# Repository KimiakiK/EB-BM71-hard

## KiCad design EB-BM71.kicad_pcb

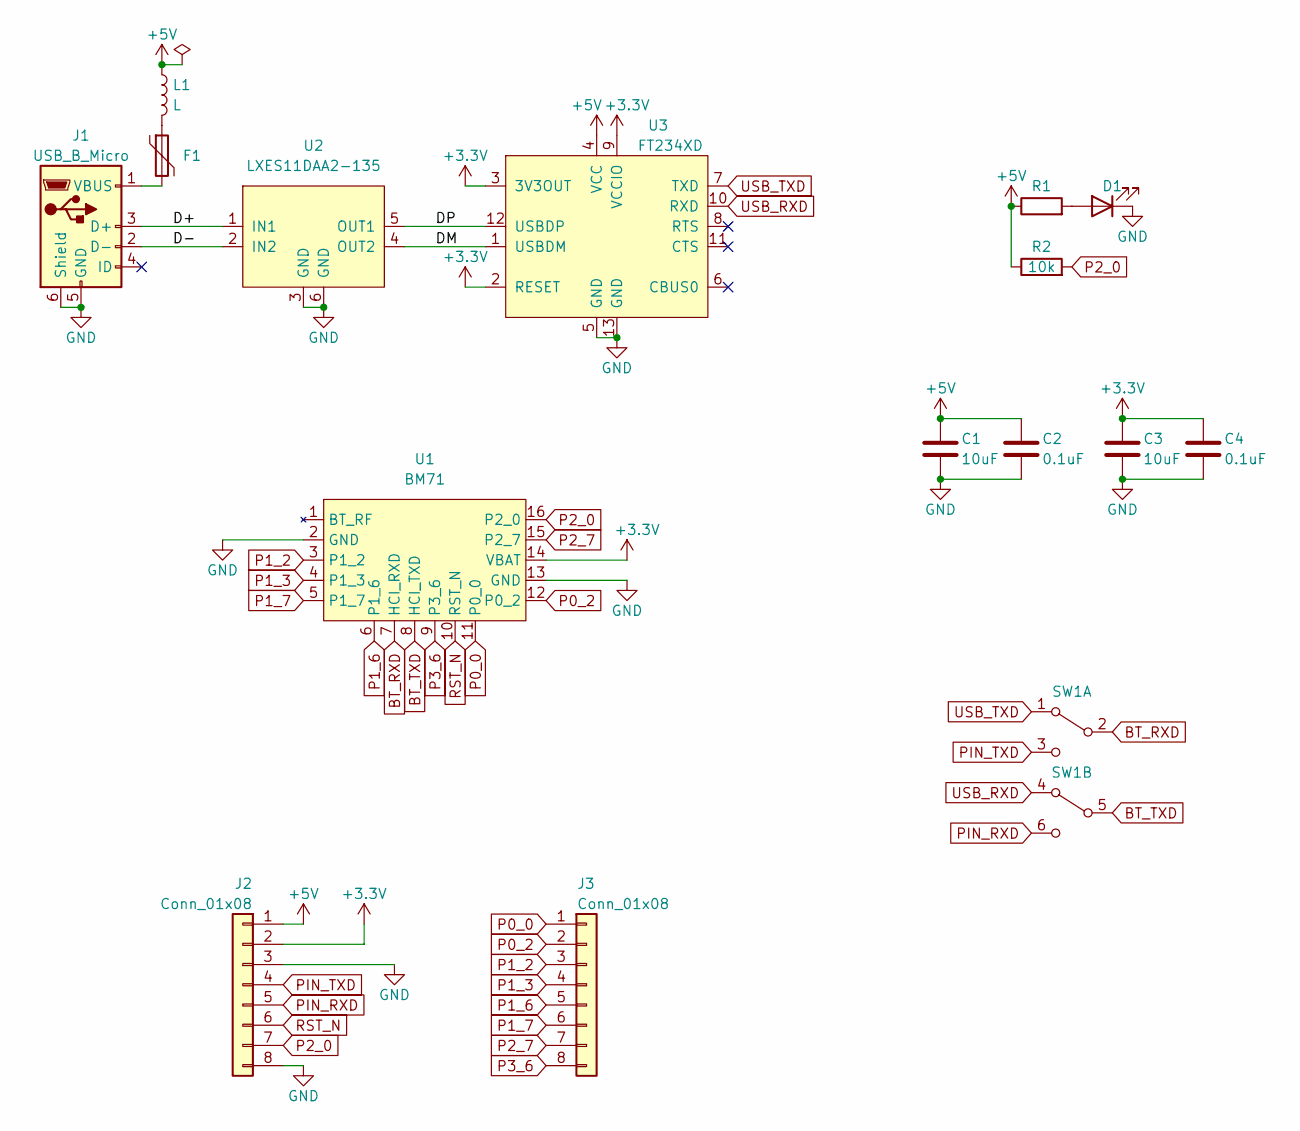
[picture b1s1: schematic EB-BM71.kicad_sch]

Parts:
C1, C3: 10uF; 1608Metric
C2, C4: 0.1uF; 1608Metric
D1: LED; 1608Metric
F1: Polyfuse; 1608Metric
J1: USB_B_Micro; UX60SC-MB-5ST
J2, J3: Conn_01x08; PinHeader_1x08_P2.54mm_Vertical
L1: L; 1608Metric
R1: R; 1608Metric
R2: 10k; 1608Metric
SW1: SW_DPDT_x2; IS-2235-G
U1: BM71
U2: LXES11DAA2-135; LXES11D
U3: FT234XD; DFN-12-1EP_3x3mm_P0.45mm_EP1.66x2.38mm

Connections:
+3.3V: C3.1, C4.1, J2.2, U1.14 (VBAT), U3.2 (RESET), U3.3 (3V3OUT), U3.9 (VCCIO)
+5V: C1.1, C2.1, J2.1, L1.1, R1.1, R2.1, U3.4 (VCC)
/D+: J1.3 (D+), U2.1 (IN1)
/D-: J1.2 (D-), U2.2 (IN2)
/DM: U2.4 (OUT2), U3.1 (USBDM)
/DP: U2.5 (OUT1), U3.12 (USBDP)
BT_RXD: SW1.2 (B), U1.7 (HCI_RXD)
BT_TXD: SW1.5 (B), U1.8 (HCI_TXD)
GND: C1.2, C2.2, C3.2, C4.2, D1.1 (K), J1.5 (GND), J1.6 (Shield), J2.3, J2.8, U1.2 (GND), U1.13 (GND), U2.3 (GND), U2.6 (GND), U3.5 (GND), U3.13 (GND)
unnamed: D1.2 (A), R1.2
unnamed: F1.1, L1.2
unnamed: F1.2, J1.1 (VBUS)
P0_0: J3.1, U1.11 (P0_0)
P0_2: J3.2, U1.12 (P0_2)
P1_2: J3.3, U1.3 (P1_2)
P1_3: J3.4, U1.4 (P1_3)
P1_6: J3.5, U1.6 (P1_6)
P1_7: J3.6, U1.5 (P1_7)
P2_0: J2.7, R2.2, U1.16 (P2_0)
P2_7: J3.7, U1.15 (P2_7)
P3_6: J3.8, U1.9 (P3_6)
PIN_RXD: J2.5, SW1.6 (C)
PIN_TXD: J2.4, SW1.3 (C)
RST_N: J2.6, U1.10 (RST_N)
USB_RXD: SW1.4 (A), U3.10 (RXD)
USB_TXD: SW1.1 (A), U3.7 (TXD)

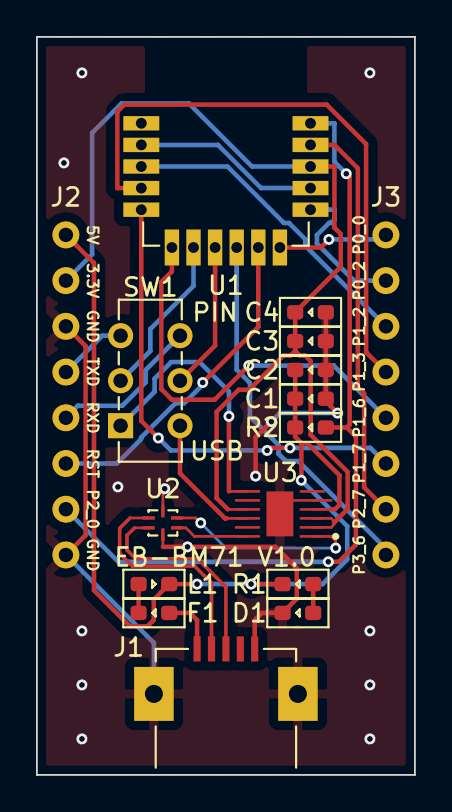
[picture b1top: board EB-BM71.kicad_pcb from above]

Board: 2 copper layers, 21.0 x 41.0 mm, 16 parts (0 on the bottom side), 26 nets.

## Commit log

2022-11-05 基板V1.0
2022-11-05 回路図追加
